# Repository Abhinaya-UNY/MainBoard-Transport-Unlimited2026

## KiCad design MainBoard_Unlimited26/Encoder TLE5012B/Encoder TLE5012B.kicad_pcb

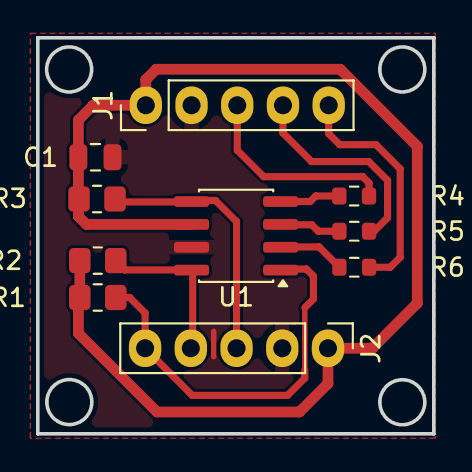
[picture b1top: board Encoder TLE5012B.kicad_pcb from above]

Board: 2 copper layers, 22.0 x 22.0 mm, 10 parts (0 on the bottom side), 11 nets.

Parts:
C1: C_Small; C_0805_2012Metric
J1, J2: Conn_01x05; PinHeader_1x05_P2.54mm_Vertical
R1, R2, R3: 2k2; R_0805_2012Metric_Pad1.20x1.40mm_HandSolder
R4, R5, R6: R_Small; R_0603_1608Metric
U1: TLE5012B; SOIC-8_3.9x4.9mm_P1.27mm

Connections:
/CSQ: J1.4, R5.1
/DATA: J1.3, R4.1
/IFA: J2.3, R3.2, U1.5 (IFA)
/IFB: J2.4, R2.2, U1.8 (IFB)
/IFC: J2.5, R1.2, U1.1 (IFC)
/SCK: J1.5, R6.1
GND: C1.2, J1.2, J2.2, U1.7 (GND)
unnamed: R5.2, U1.3 (CSQ)
unnamed: R4.2, U1.4 (DATA)
unnamed: R6.2, U1.2 (SCK)
VCC: C1.1, J1.1, J2.1, R1.1, R2.1, R3.1, U1.6 (VDD)

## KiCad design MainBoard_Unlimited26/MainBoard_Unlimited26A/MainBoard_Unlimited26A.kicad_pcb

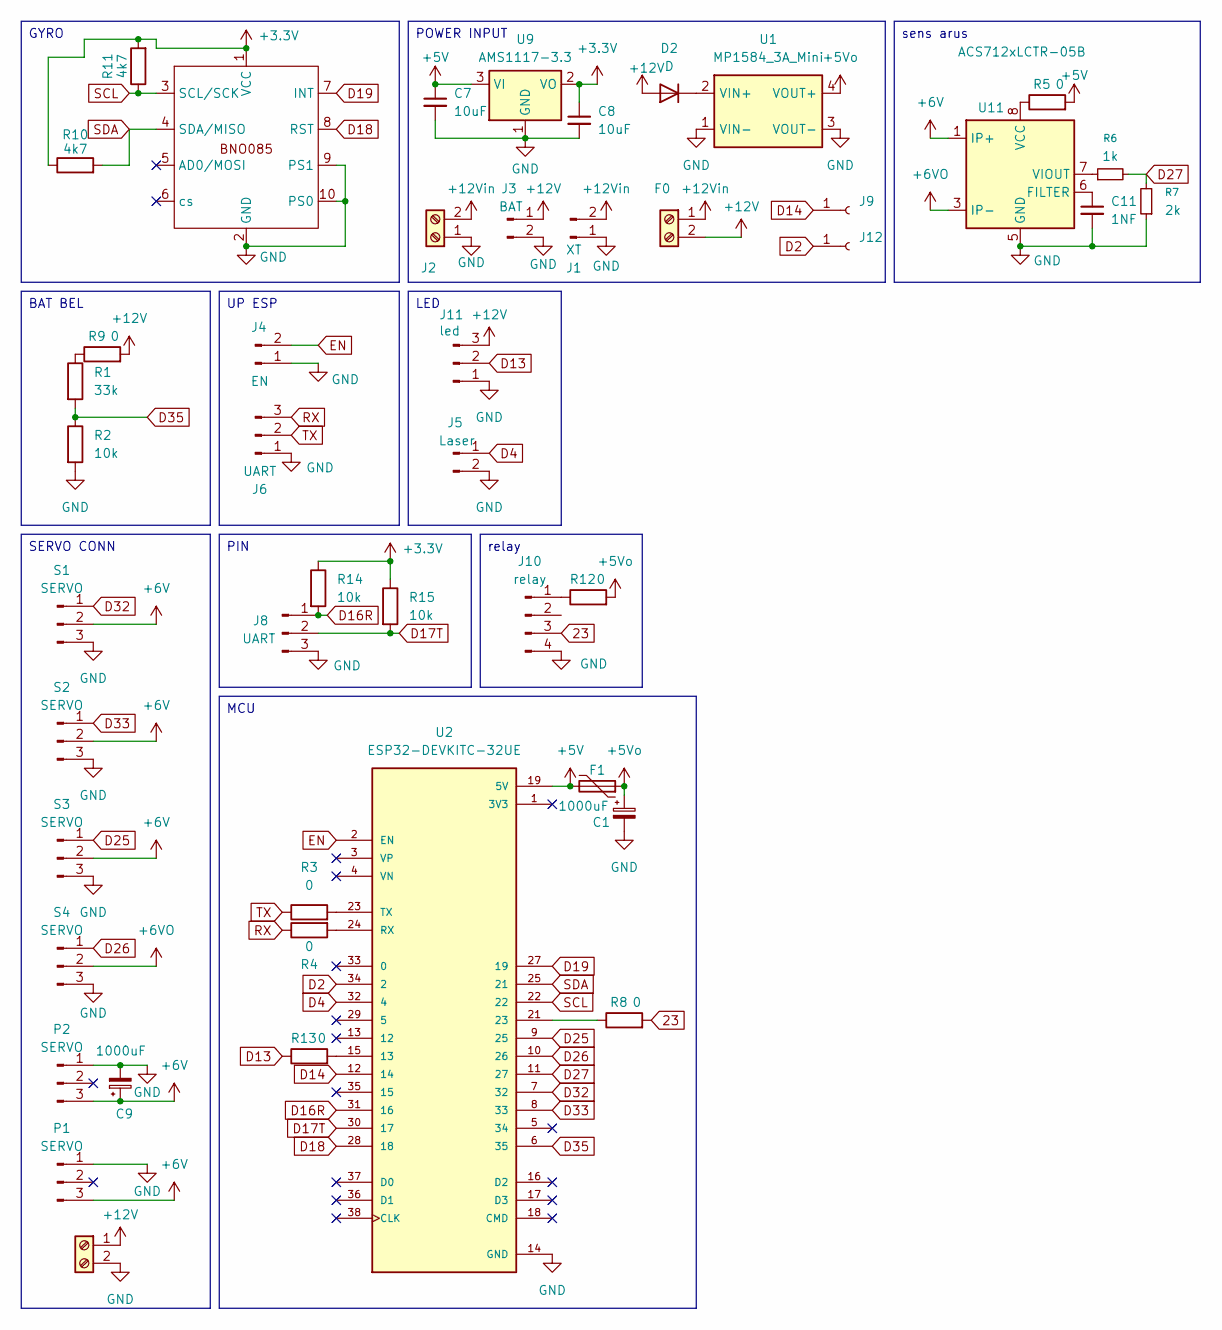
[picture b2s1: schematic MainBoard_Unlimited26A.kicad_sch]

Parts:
C1, C9: 1000uF; CP_Radial_D10.0mm_P5.00mm
C7, C8: 10uF; C_0805_2012Metric_Pad1.18x1.45mm_HandSolder
C11: 1NF; C_0805_2012Metric_Pad1.18x1.45mm_HandSolder
D2: D; D_SMA
F0: Screw_Terminal_01x02; TerminalBlock_MaiXu_MX126-5.0-02P_1x02_P5.00mm
F1: Polyfuse; Fuse_1812_4532Metric
J1: XT; AMASS_XT30U-F_1x02_P5.0mm_Vertical
J2: Screw_Terminal_01x02; TerminalBlock_MaiXu_MX126-5.0-02P_1x02_P5.00mm
J3: BAT; JST_XH_B2B-XH-A_1x02_P2.50mm_Vertical
J4: EN; PinHeader_1x02_P2.54mm_Vertical
J5: Laser; JST_XH_B2B-XH-A_1x02_P2.50mm_Vertical
J6: UART; JST_XH_S3B-XH-A_1x03_P2.50mm_Horizontal
J8: UART; JST_XH_S3B-XH-A-1_1x03_P2.50mm_Horizontal
J9, J12: Conn_01x01_Socket; PinHeader_1x01_P2.54mm_Vertical
J10: relay; JST_XH_B4B-XH-A_1x04_P2.50mm_Vertical
J11: led; JST_XH_B3B-XH-A_1x03_P2.50mm_Vertical
P1, P2: SERVO; JST_XH_B3B-XH-A_1x03_P2.50mm_Vertical
R1: 33k; R_1206_3216Metric_Pad1.30x1.75mm_HandSolder
R2, R14, R15: 10k; R_0805_2012Metric_Pad1.20x1.40mm_HandSolder
R3, R4, R5, R8, R9, R12, R13: 0; R_1206_3216Metric_Pad1.30x1.75mm_HandSolder
R6: 1k; R_0805_2012Metric_Pad1.20x1.40mm_HandSolder
R7: 2k; R_0805_2012Metric_Pad1.20x1.40mm_HandSolder
R10, R11: 4k7; R_0805_2012Metric_Pad1.20x1.40mm_HandSolder
S0: Screw_Terminal_01x02; TerminalBlock_MaiXu_MX126-5.0-02P_1x02_P5.00mm
S1, S2, S3, S4: SERVO; JST_XH_B3B-XH-A_1x03_P2.50mm_Vertical
U1: MP1584_3A_Mini; MP1584_Module
U2: ESP32-DEVKITC-32UE; ESPRESSIF_ESP32-DEVKITC-32UE; PARTREV V4
U8: MPU6050/BNO085 I2C; PinSocket_1x10_P2.54mm_Vertical
U9: AMS1117-3.3; SOT-223-3_TabPin2
U11: ACS712xLCTR-05B; SOIC-8_3.9x4.9mm_P1.27mm

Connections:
23: J10.3, R8.2
+3.3V: C8.1, R10.1, R11.2, R14.1, R15.1, U8.1 (VCC), U9.2 (VO)
+5V: C7.1, F1.2, R5.2, U2.19 (5V), U9.3 (VI)
+5Vo: C1.1, F1.1, R12.2, U1.4 (VOUT+)
+6V: C9.1, P1.3, P2.3, S1.2, S2.2, S3.2, U11.1 (IP+), U11.2 (IP+)
+6VO: S4.2, U11.3 (IP-), U11.4 (IP-)
+12V: D2.2 (A), F0.2, J3.1, J11.3, R9.2, S0.1
+12Vin: F0.1, J1.2, J2.2
D2: J12.1 (Pin_1_1), U2.34 (2)
D4: J5.1, U2.32 (4)
D13: J11.2, R13.1
D14: J9.1 (Pin_1_1), U2.12 (14)
D16R: J8.1, R14.2, U2.31 (16)
D17T: J8.2, R15.2, U2.30 (17)
D18: U2.28 (18), U8.8 (RST)
D19: U2.27 (19), U8.7 (INT)
D25: S3.1, U2.9 (25)
D26: S4.1, U2.10 (26)
D27: R6.2, R7.2, U2.11 (27)
D32: S1.1, U2.7 (32)
D33: S2.1, U2.8 (33)
D35: R1.2, R2.1, U2.6 (35)
EN: J4.2, U2.2 (EN)
GND: C1.2, C7.2, C8.2, C9.2, C11.2, J1.1, J2.1, J3.2, J4.1, J5.2, J6.1, J8.3, J10.4, J11.1, P1.1, P2.1, R2.2, R7.1, S0.2, S1.3, S2.3, S3.3, S4.3, U1.1 (VIN-), U1.3 (VOUT-), U2.14 (GND), U2.20 (GND), U2.26 (GND), U8.2 (GND), U8.9 (PS1), U8.10 (PS0), U9.1 (GND), U11.5 (GND)
unnamed: D2.1 (K), U1.2 (VIN+)
unnamed: J10.1, R12.1
unnamed: R1.1, R9.1
unnamed: R13.2, U2.15 (13)
unnamed: R8.1, U2.21 (23)
unnamed: R4.2, U2.24 (RX)
unnamed: R3.2, U2.23 (TX)
unnamed: C11.1, U11.6 (FILTER)
unnamed: R5.1, U11.8 (VCC)
unnamed: R6.1, U11.7 (VIOUT)
RX: J6.3, R4.1
SCL: R11.1, U2.22, U8.3 (SCL/SCK)
SDA: R10.2, U2.25 (21), U8.4 (SDA/MISO)
TX: J6.2, R3.1

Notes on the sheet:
PIN
UP ESP
sens arus
POWER INPUT
MCU
BAT BEL
GYRO
LED
SERVO CONN
relay

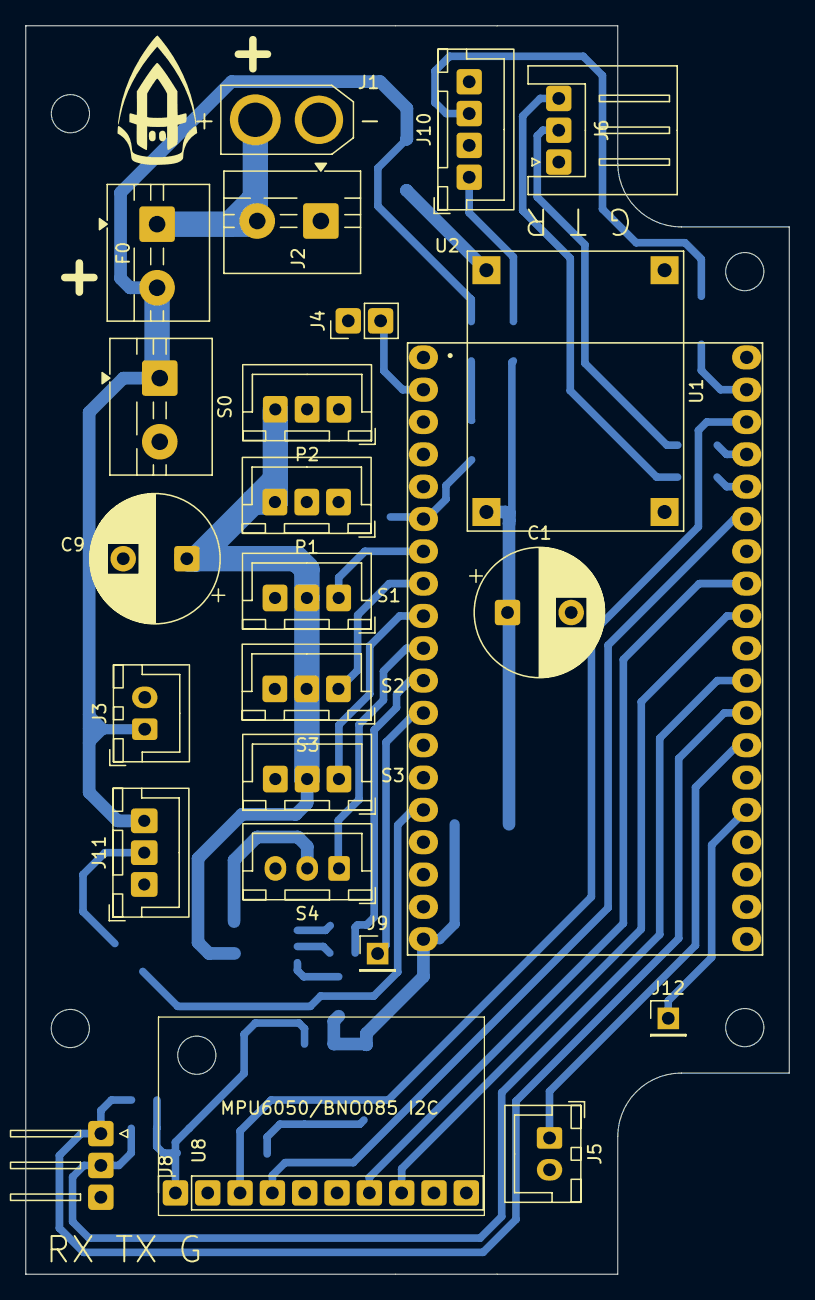
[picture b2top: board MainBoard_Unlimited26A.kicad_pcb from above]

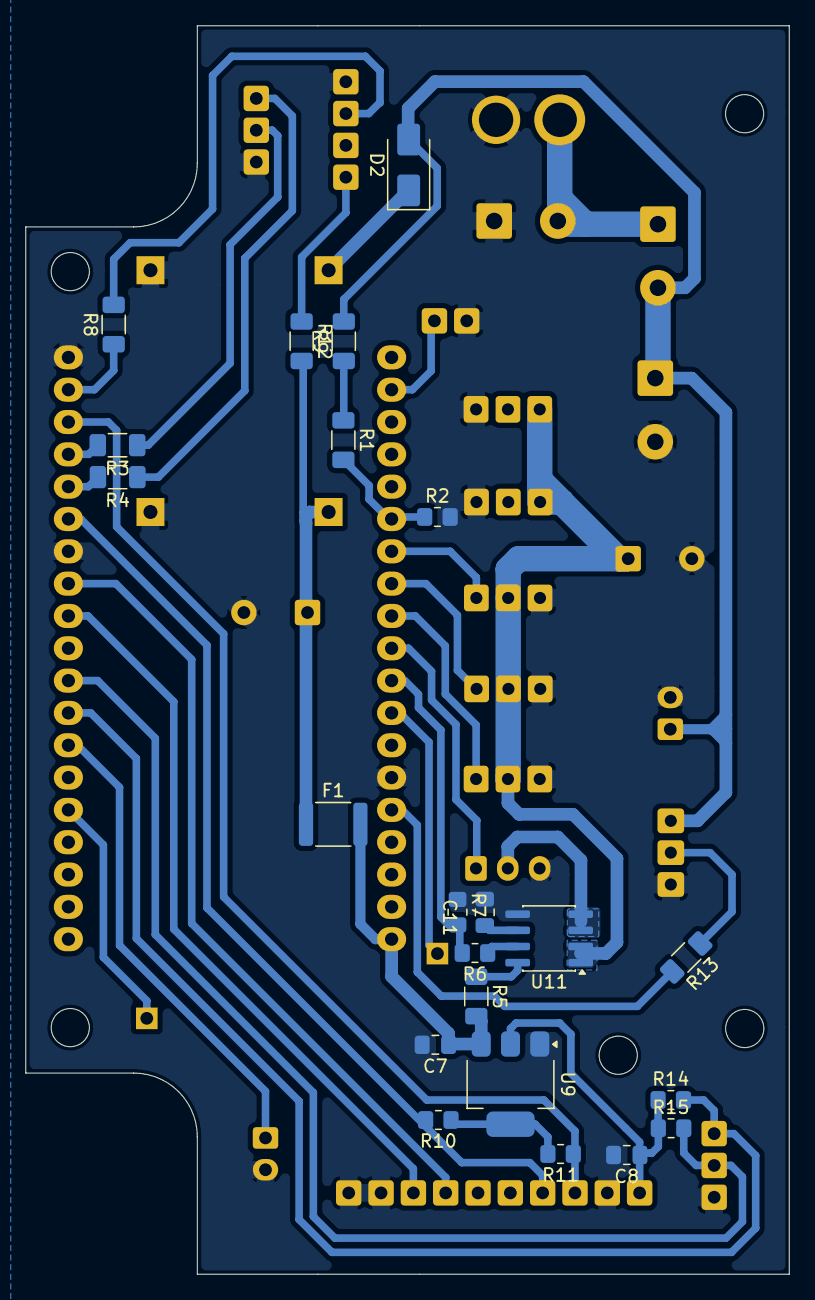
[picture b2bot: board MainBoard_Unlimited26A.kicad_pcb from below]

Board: 2 copper layers, 60.0 x 98.1 mm, 46 parts (22 on the bottom side), 38 nets.

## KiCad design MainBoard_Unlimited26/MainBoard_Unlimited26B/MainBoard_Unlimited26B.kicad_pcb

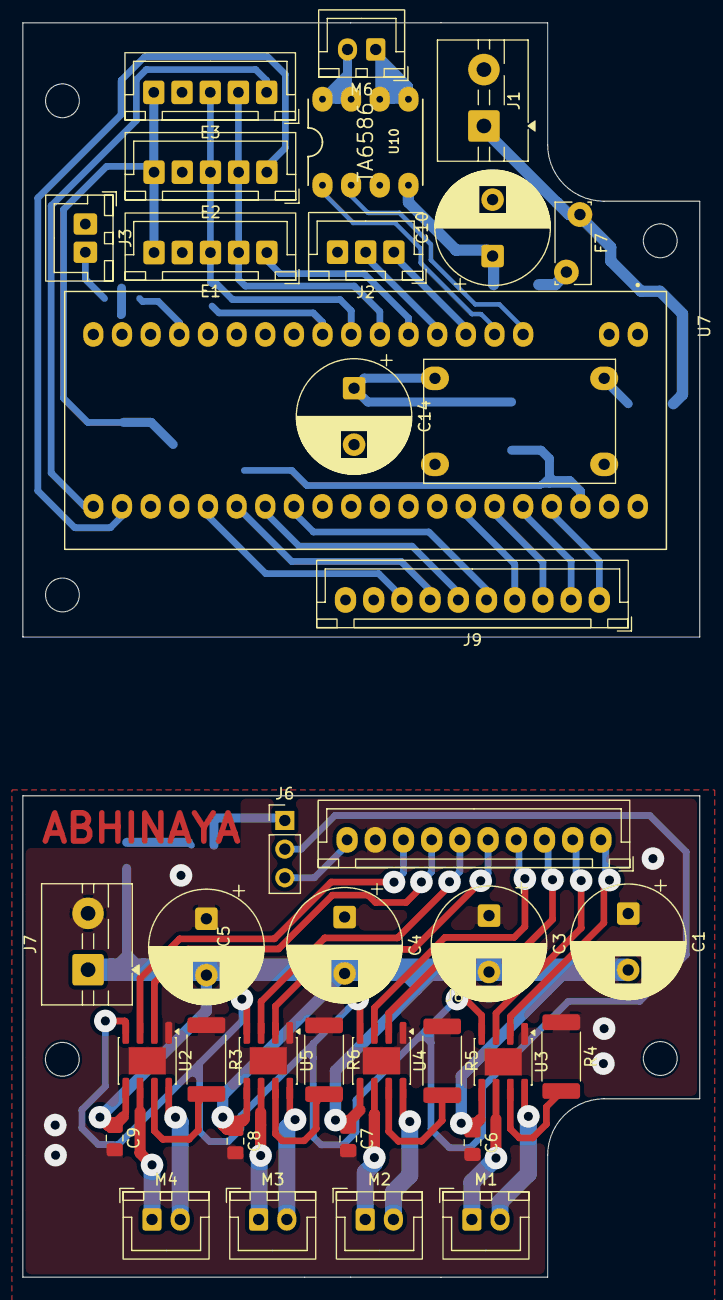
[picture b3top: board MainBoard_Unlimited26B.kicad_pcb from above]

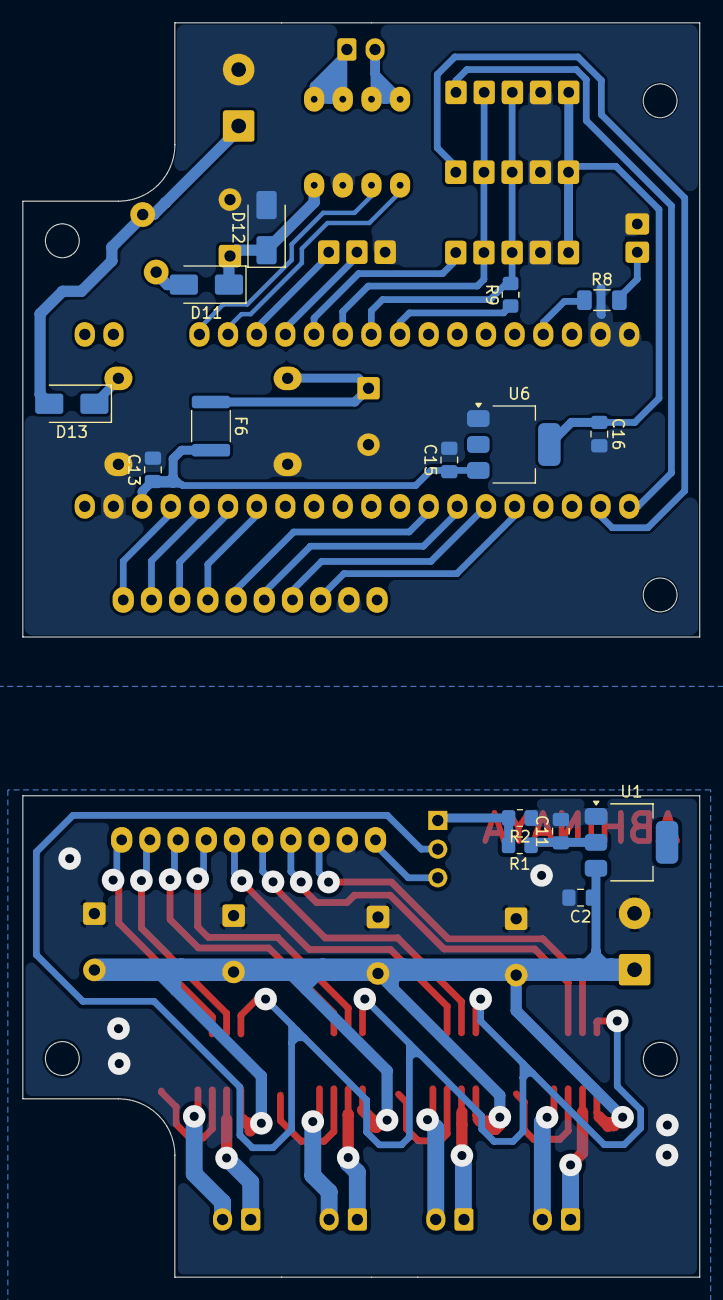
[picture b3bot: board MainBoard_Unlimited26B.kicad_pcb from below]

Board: 2 copper layers, 60.0 x 111.2 mm, 52 parts (15 on the bottom side), 46 nets.

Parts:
C1, C3, C4, C5, C10, C14: 1000uF; CP_Radial_D10.0mm_P5.00mm
C2, C11, C16: 10uF; C_0805_2012Metric_Pad1.18x1.45mm_HandSolder
C6, C7, C8, C9: 100nF; C_0805_2012Metric_Pad1.18x1.45mm_HandSolder
C13: 0.1uF; C_0805_2012Metric_Pad1.18x1.45mm_HandSolder
C15: 33uF; C_0805_2012Metric_Pad1.18x1.45mm_HandSolder
D11, D12, D13: D_Schottky; D_SMA
E1, E2, E3: Encoder; JST_XH_B5B-XH-A_1x05_P2.50mm_Vertical
F6: Polyfuse; Fuse_1812_4532Metric
F7: Polyfuse; Fuse_Bourns_MF-RG300
J1, J7: power; TerminalBlock_MaiXu_MX126-5.0-02P_1x02_P5.00mm
J2: Conn_01x03_Pin; JST_XH_B3B-XH-A_1x03_P2.50mm_Vertical
J3: JST_XH_B2B-XH-A_1x02_P2.50mm_Vertical
J6: vreff mode; PinHeader_1x03_P2.54mm_Vertical
J8, J9: mconn; JST_XH_B10B-XH-A_1x10_P2.50mm_Vertical
M1, M2, M3, M4, M6: JST_XH_B2B-XH-A_1x02_P2.50mm_Vertical
R1: 10k; R_0805_2012Metric_Pad1.20x1.40mm_HandSolder
R2: 6k8; R_0805_2012Metric_Pad1.20x1.40mm_HandSolder
R3, R4, R5, R6: 0.1; R_2512_6332Metric_Pad1.40x3.35mm_HandSolder
R8: 0; R_1206_3216Metric_Pad1.30x1.75mm_HandSolder
R9: 1k; R_0805_2012Metric_Pad1.20x1.40mm_HandSolder
U1: AMS1117-5.0; SOT-223-3_TabPin2
U2, U3, U4, U5: A4950E; SOIC-8-1EP_3.9x4.9mm_P1.27mm_EP2.41x3.3mm
U6: AMS1117-3.3; SOT-223-3_TabPin2
U7: ZC323000; MODULE_ZC323000
U8: MP1584_3A_Mini; Mini360
U10: TA6586; TA6586-FOOTPRINT

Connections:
1O1: M1.1, U3.6 (OUT1)
1O2: M1.2, U3.8 (OUT2)
2O1: M2.1, U4.6 (OUT1)
2O2: M2.2, U4.8 (OUT2)
2V: J6.1, R1.2, R2.2
3O1: M3.1, U5.6 (OUT1)
3O2: M3.2, U5.8 (OUT2)
4O1: M4.1, U2.6 (OUT1)
4O2: M4.2, U2.8 (OUT2)
+3.3V: C16.1, E1.5, E2.5, E3.5, U6.2 (VO)
+5V: C13.1, C15.1, F6.2, U6.3 (VI), U7.38 (5V)
+12V: C1.2, C2.1, C3.2, C4.2, C5.2, C6.1, C7.1, C8.1, C9.1, J7.1, U1.3 (VI), U2.5 (VBB), U3.5 (VBB), U4.5 (VBB), U5.5 (VBB)
+12Vs: D13.2 (A), F7.1, J1.1
B6: M6.2, U10.BO1, U10.BO2
DATA: E1.3, E2.3, E3.3, R9.2, U7.11 (A6)
F6: M6.1, U10.FO1, U10.FO2
GND: C1.1, C2.2, C3.1, C4.1, C5.1, C6.2, C7.2, C8.2, C9.2, C10.2, C11.2, C13.2, C14.2, C15.2, C16.2, D12.2 (A), E1.4, E2.4, E3.4, J1.2, J2.3, J3.1, J7.2, J8.9, J9.9, R2.1, R3.1, R4.1, R5.1, R6.1, U1.1 (GND), U2.1 (GND), U2.9 (PAD), U3.1 (GND), U3.9 (PAD), U4.1 (GND), U4.9 (PAD), U5.1 (GND), U5.9 (PAD), U6.1 (GND), U7.19 (G), U7.20 (G), U7.39 (G), U8.1 (VIN-), U8.3 (VOUT-), U10.GND
MOSI: R9.1, U7.12 (A7)
unnamed: D11.2 (A), F7.2
unnamed: C10.1, D11.1 (K), D12.1 (K), U10.VCC
unnamed: D13.1 (K), U8.2 (VIN+)
unnamed: C11.1, R1.1, U1.2 (VO)
unnamed: R3.2, U2.7 (LSS)
unnamed: R4.2, U3.7 (LSS)
unnamed: R5.2, U4.7 (LSS)
unnamed: R6.2, U5.7 (LSS)
unnamed: C14.1, F6.1, U8.4 (VOUT+)
PA0: U7.5 (A0), U10.FI
PA1: U7.6 (A1), U10.BI
PA8: J8.8, J9.8, U2.3 (IN1), U7.25 (A8)
PA9: J8.7, J9.7, U2.2 (IN2), U7.26 (A9)
PA10: J8.6, J9.6, U5.3 (IN1), U7.27 (A10)
PA11: J8.5, J9.5, U5.2 (IN2), U7.28 (A11)
PB6: J8.4, J9.4, U4.3 (IN1), U7.34 (B6)
PB7: J8.3, J9.3, U4.2 (IN2), U7.35 (B7)
PB8: J8.2, J9.2, U3.3 (IN1), U7.36 (B8)
PB9: J8.1, J9.1, U3.2 (IN2), U7.37 (B9)
R: J3.2, R8.1, R8.2, U7.17 (R)
REFF: J6.2, U2.4 (VREF), U3.4 (VREF), U4.4 (VREF), U5.4 (VREF)
RX: J2.2, U7.8 (A3)
SCK: E1.2, E2.2, E3.2, U7.10 (A5)
SS1: E1.1, U7.9 (A4)
SS2: E2.1, U7.22 (B13)
SS3: E3.1, U7.21 (B12)
TX: J2.1, U7.7 (A2)
Vreff: J6.3, J8.10, J9.10

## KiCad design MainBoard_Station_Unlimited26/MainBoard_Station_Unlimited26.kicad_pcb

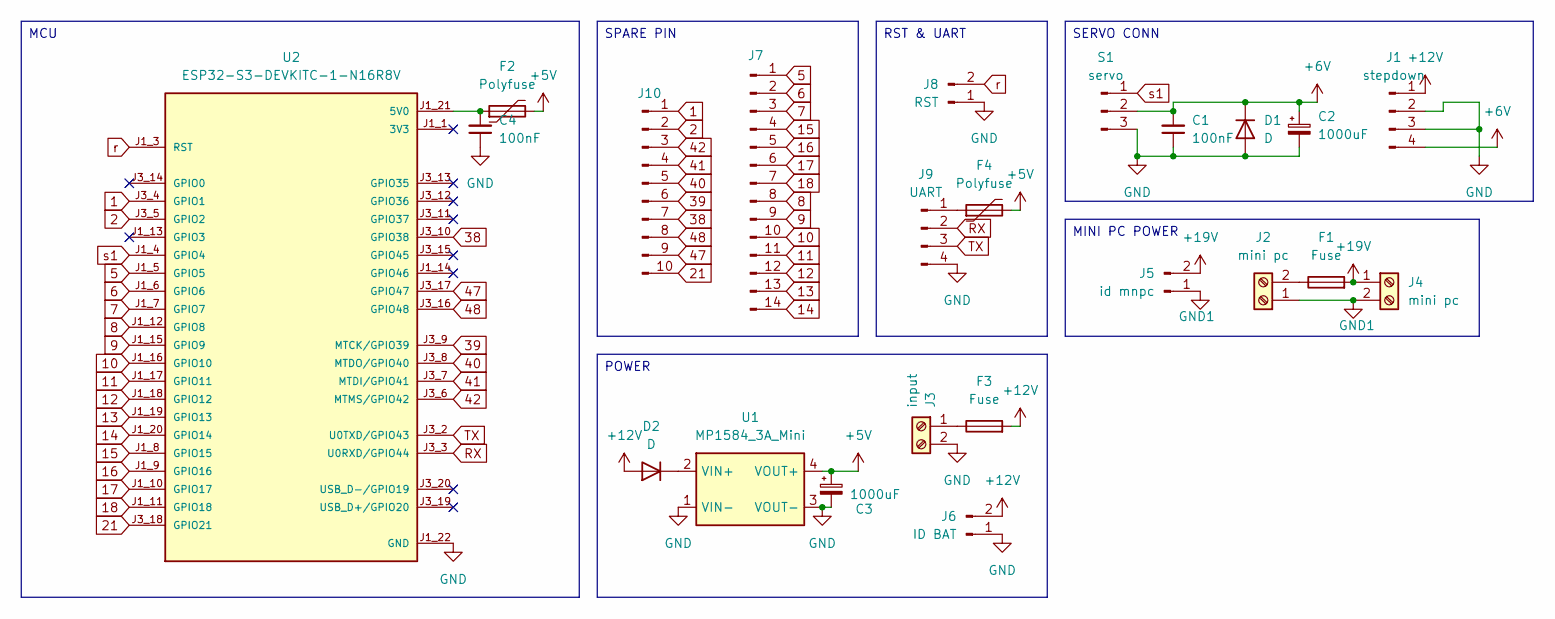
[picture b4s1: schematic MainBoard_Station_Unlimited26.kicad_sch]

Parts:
C1, C4: 100nF; C_0805_2012Metric_Pad1.18x1.45mm_HandSolder
C2, C3: 1000uF; CP_Radial_D10.0mm_P5.00mm
D1, D2: D; D_SMA
F1, F3: Fuse; FUSE_4628
F2, F4: Polyfuse; Fuse_1812_4532Metric
J1: stepdown; xl4015-modul
J2, J4: mini pc; TerminalBlock_MaiXu_MX126-5.0-02P_1x02_P5.00mm
J3: input; TerminalBlock_MaiXu_MX126-5.0-02P_1x02_P5.00mm
J5: id mnpc; JST_XH_B2B-XH-A_1x02_P2.50mm_Vertical
J6: ID BAT; JST_XH_B2B-XH-A_1x02_P2.50mm_Vertical
J7: Conn_01x14_Pin; PinHeader_1x14_P2.54mm_Vertical
J8: RST; JST_XH_B2B-XH-A_1x02_P2.50mm_Vertical
J9: UART; JST_XH_B4B-XH-A_1x04_P2.50mm_Vertical
J10: Conn_01x10_Pin; PinSocket_1x10_P2.54mm_Vertical
S1: servo; JST_XH_B3B-XH-A_1x03_P2.50mm_Vertical
U1: MP1584_3A_Mini; MP1584_Module
U2: ESP32-S3-DEVKITC-1-N16R8V; XCVR_ESP32-S3-DEVKITC-1-N16R8V; PARTREV 1.1

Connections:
1: J10.1, U2.J3_4 (GPIO1)
2: J10.2, U2.J3_5 (GPIO2)
5: J7.1, U2.J1_5 (GPIO5)
6: J7.2, U2.J1_6 (GPIO6)
7: J7.3, U2.J1_7 (GPIO7)
8: J7.8, U2.J1_12 (GPIO8)
9: J7.9, U2.J1_15 (GPIO9)
10: J7.10, U2.J1_16 (GPIO10)
11: J7.11, U2.J1_17 (GPIO11)
12: J7.12, U2.J1_18 (GPIO12)
13: J7.13, U2.J1_19 (GPIO13)
14: J7.14, U2.J1_20 (GPIO14)
15: J7.4, U2.J1_8 (GPIO15)
16: J7.5, U2.J1_9 (GPIO16)
17: J7.6, U2.J1_10 (GPIO17)
18: J7.7, U2.J1_11 (GPIO18)
21: J10.10, U2.J3_18 (GPIO21)
38: J10.7, U2.J3_10 (GPIO38)
39: J10.6, U2.J3_9 (MTCK/GPIO39)
40: J10.5, U2.J3_8 (MTDO/GPIO40)
41: J10.4, U2.J3_7 (MTDI/GPIO41)
42: J10.3, U2.J3_6 (MTMS/GPIO42)
47: J10.9, U2.J3_17 (GPIO47)
48: J10.8, U2.J3_16 (GPIO48)
+5V: C3.1, F2.2, F4.2, U1.4 (VOUT+)
+6V: C1.2, C2.1, D1.1 (K), J1.4, S1.2
+12V: D2.2 (A), F3.2, J1.1, J6.2
GND: C1.1, C2.2, C3.2, C4.1, D1.2 (A), J1.2, J1.3, J3.2, J6.1, J8.1, J9.4, S1.3, U1.1 (VIN-), U1.3 (VOUT-), U2.J1_22 (GND), U2.J3_1 (GND), U2.J3_21 (GND), U2.J3_22 (GND)
GND1: J2.1, J4.2, J5.1
unnamed: D2.1 (K), U1.2 (VIN+)
unnamed: F1.1, J2.2
unnamed: F3.1, J3.1
unnamed: F1.2, J4.1, J5.2
unnamed: F4.1, J9.1
unnamed: C4.2, F2.1, U2.J1_21 (5V0)
RX: J9.2, U2.J3_3 (U0RXD/GPIO44)
TX: J9.3, U2.J3_2 (U0TXD/GPIO43)
s1: S1.1, U2.J1_4 (GPIO4)

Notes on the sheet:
POWER
MINI PC POWER
MCU
SPARE PIN
RST & UART
SERVO CONN

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
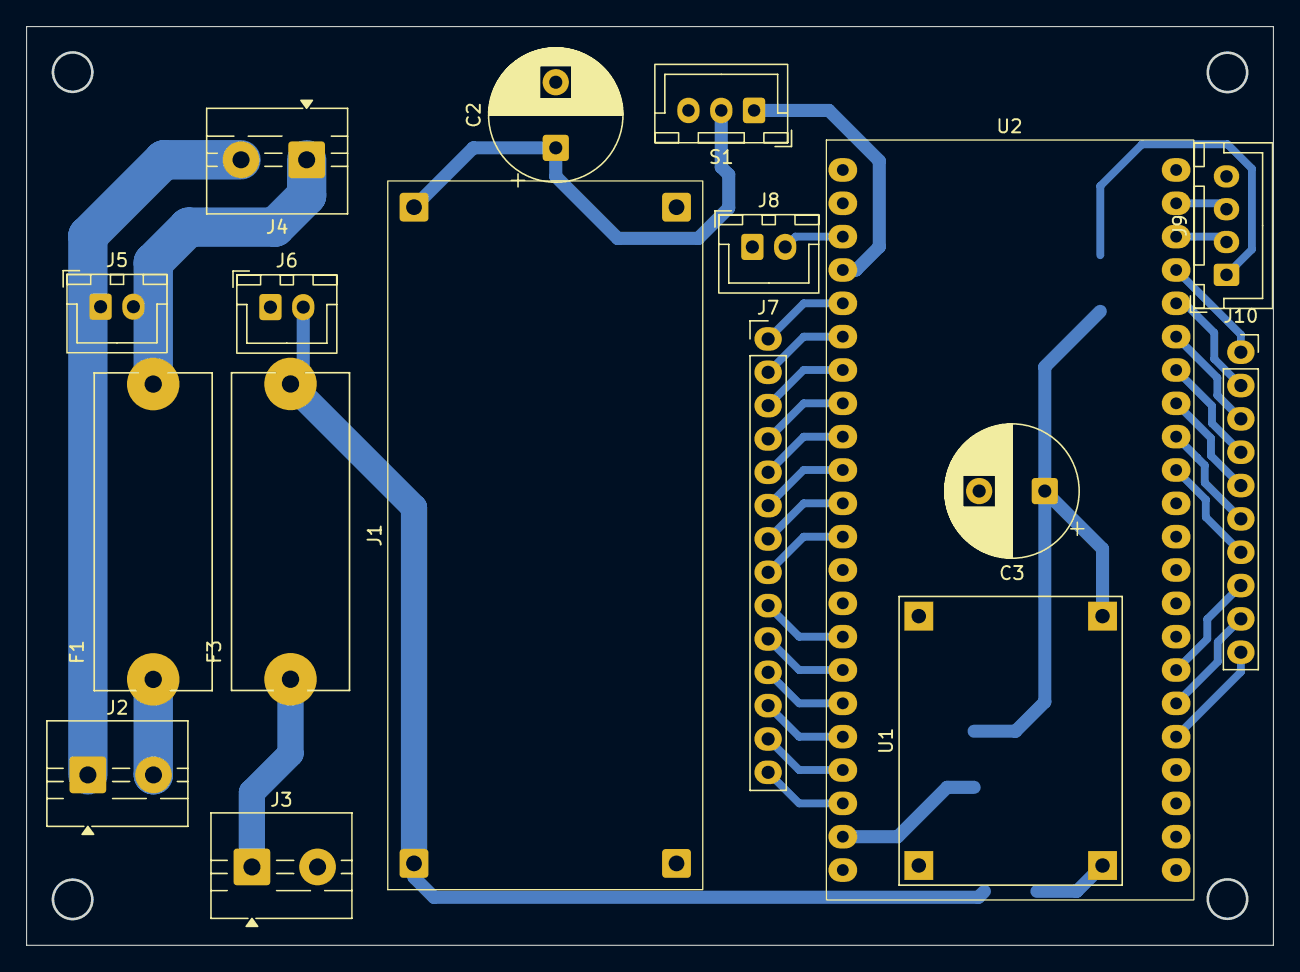
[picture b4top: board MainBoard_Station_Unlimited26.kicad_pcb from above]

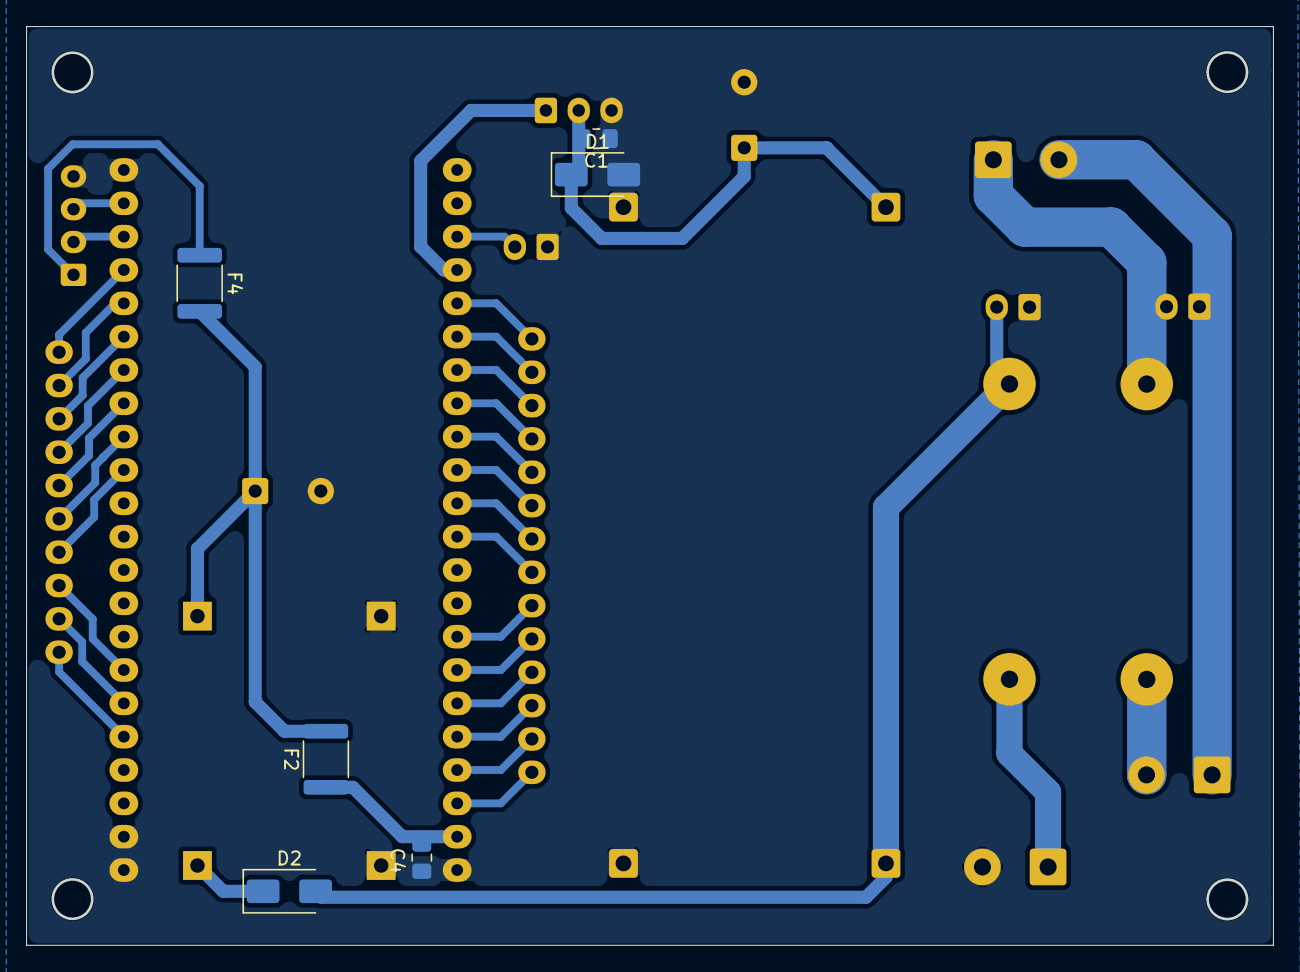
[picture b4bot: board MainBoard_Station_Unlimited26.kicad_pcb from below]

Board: 2 copper layers, 95.0 x 70.0 mm, 23 parts (6 on the bottom side), 38 nets.

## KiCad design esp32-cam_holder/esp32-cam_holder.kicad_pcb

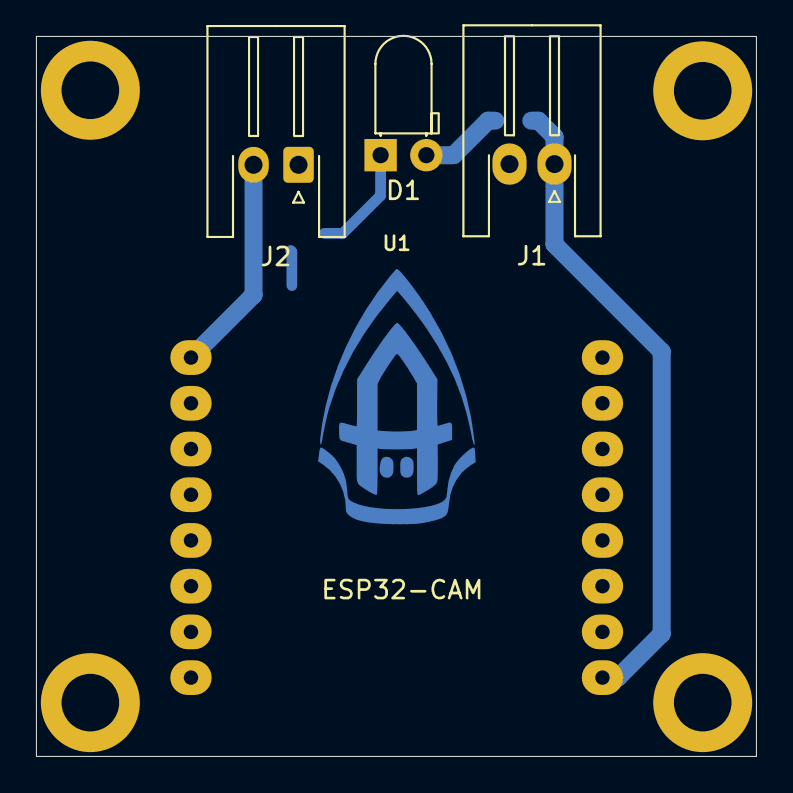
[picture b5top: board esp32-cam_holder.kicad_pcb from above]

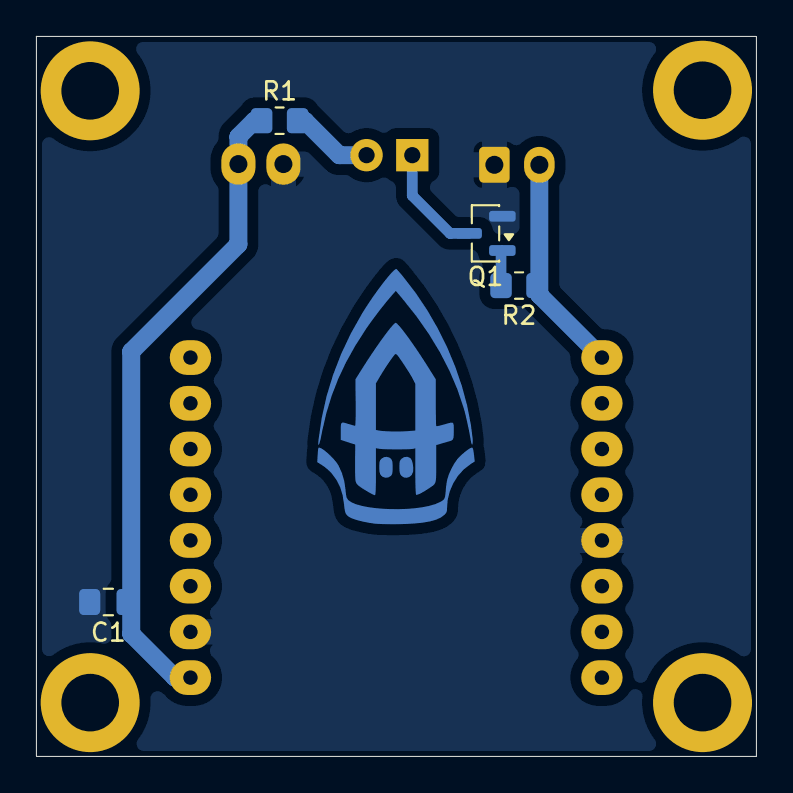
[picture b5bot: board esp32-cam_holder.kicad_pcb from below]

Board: 2 copper layers, 40.0 x 40.0 mm, 8 parts (4 on the bottom side), 6 nets.

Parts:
C1: 100nF; C_0805_2012Metric_Pad1.18x1.45mm_HandSolder
D1: LED; LED_D3.0mm_Horizontal_O1.27mm_Z6.0mm
J1: power; JST_XH_S2B-XH-A-1_1x02_P2.50mm_Horizontal
J2: RST; JST_XH_S2B-XH-A-1_1x02_P2.50mm_Horizontal
Q1: MMBT3904; SOT-23
R1: 220; R_0805_2012Metric_Pad1.20x1.40mm_HandSolder
R2: 1k; R_0805_2012Metric_Pad1.20x1.40mm_HandSolder
U1: ESP32-CAM

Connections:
+5V: C1.1, J1.1, R1.1, U1.5V
GND: C1.2, J1.2, J2.1, Q1.2 (E), U1.GND, U1.GND2
unnamed: D1.2 (A), R1.2
unnamed: D1.1 (K), Q1.3 (C)
unnamed: Q1.1 (B), R2.2
RST: J2.2, R2.1, U1.GND1
